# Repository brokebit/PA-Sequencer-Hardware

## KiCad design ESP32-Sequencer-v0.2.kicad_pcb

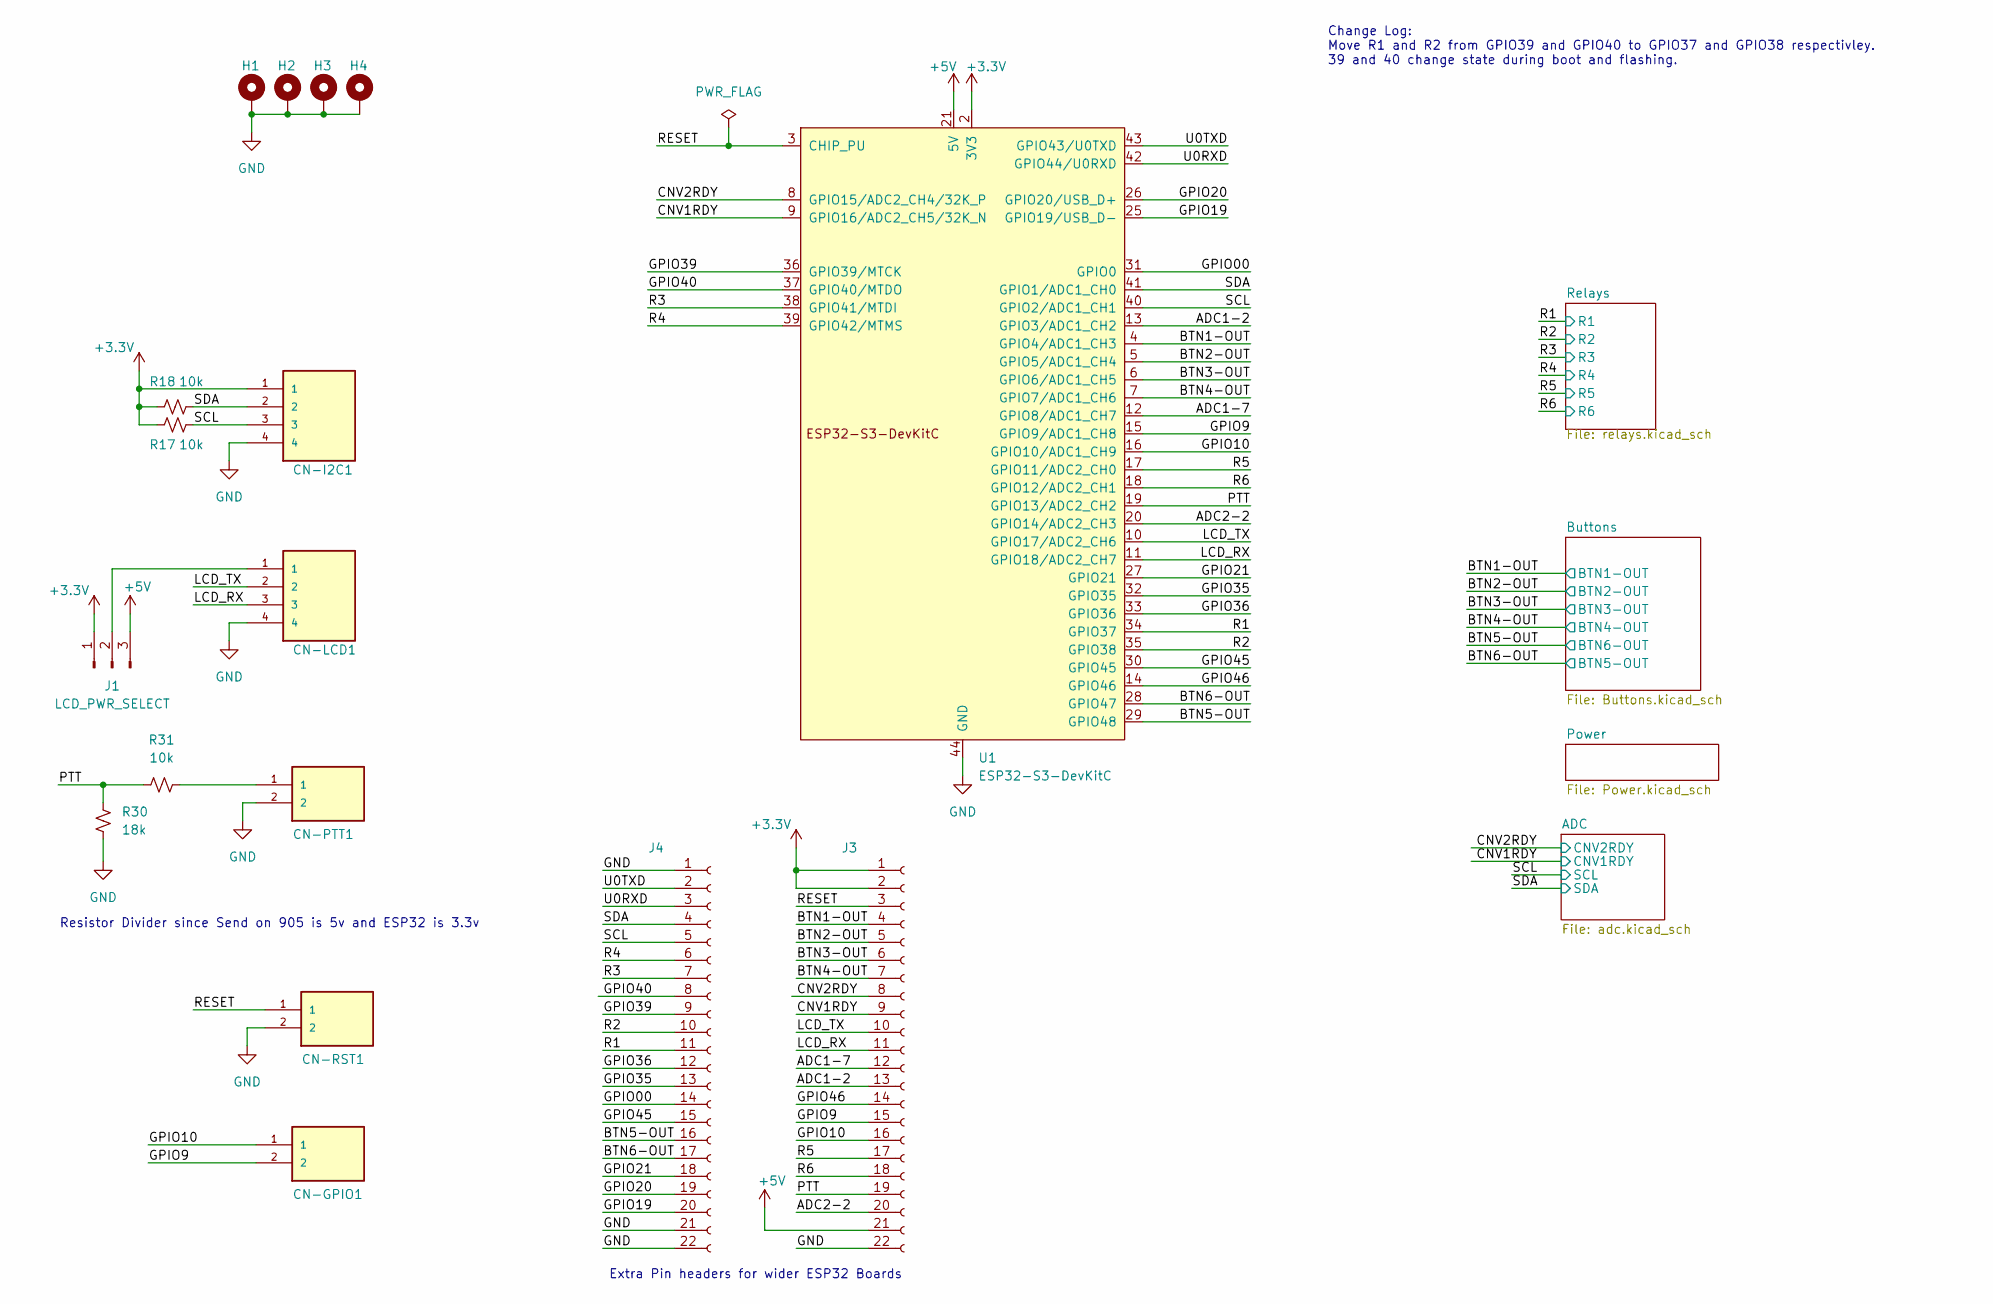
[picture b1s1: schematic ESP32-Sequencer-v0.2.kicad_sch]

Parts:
CN-GPIO1: TBP02R1-381-02OR; CUI_TBP02R1-381-02OR
CN-I2C1: TBP02R1-381-04OR; CUI_TBP02R1-381-04OR
CN-LCD1: TBP02R1-381-04OR; CUI_TBP02R1-381-04OR
CN-PTT1: TBP02R1-381-02OR; CUI_TBP02R1-381-02OR
CN-RST1: TBP02R1-381-02OR; CUI_TBP02R1-381-02OR
H1, H2, H3, H4: MountingHole_Pad; MountingHole_3.2mm_M3_Pad
J1: LCD_PWR_SELECT; PinHeader_1x03_P2.54mm_Vertical
J3, J4: Conn_01x22_Socket; PinSocket_1x22_P2.54mm_Vertical
R17, R18, R31: 10k; R_0805_2012Metric
R30: 18k; R_0805_2012Metric
U1: ESP32-S3-DevKitC

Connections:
+3.3V: CN-I2C1.1, J1.1, J3.1, J3.2, R17.1, R18.1, U1.1 (3V3), U1.2 (3V3); also elsewhere on the board
+5V: J1.3, J3.21, U1.21 (5V); also elsewhere on the board
/ADC1-2: J3.13, U1.13 (GPIO3/ADC1_CH2)
/ADC1-7: J3.12, U1.12 (GPIO8/ADC1_CH7)
/ADC2-2: J3.20, U1.20 (GPIO14/ADC2_CH3)
/BTN1-OUT: J3.4, U1.4 (GPIO4/ADC1_CH3); also elsewhere on the board
/BTN2-OUT: J3.5, U1.5 (GPIO5/ADC1_CH4); also elsewhere on the board
/BTN3-OUT: J3.6, U1.6 (GPIO6/ADC1_CH5); also elsewhere on the board
/BTN4-OUT: J3.7, U1.7 (GPIO7/ADC1_CH6); also elsewhere on the board
/BTN5-OUT: J4.16, U1.29 (GPIO48); also elsewhere on the board
/BTN6-OUT: J4.17, U1.28 (GPIO47); also elsewhere on the board
/CNV1RDY: J3.9, U1.9 (GPIO16/ADC2_CH5/32K_N); also elsewhere on the board
/CNV2RDY: J3.8, U1.8 (GPIO15/ADC2_CH4/32K_P); also elsewhere on the board
/GPIO00: J4.14, U1.31 (GPIO0)
/GPIO9: CN-GPIO1.2, J3.15, U1.15 (GPIO9/ADC1_CH8)
/GPIO10: CN-GPIO1.1, J3.16, U1.16 (GPIO10/ADC1_CH9)
/GPIO19: J4.20, U1.25 (GPIO19/USB_D-)
/GPIO20: J4.19, U1.26 (GPIO20/USB_D+)
/GPIO21: J4.18, U1.27 (GPIO21)
/GPIO35: J4.13, U1.32 (GPIO35)
/GPIO36: J4.12, U1.33 (GPIO36)
/GPIO39: J4.9, U1.36 (GPIO39/MTCK)
/GPIO40: J4.8, U1.37 (GPIO40/MTDO)
/GPIO45: J4.15, U1.30 (GPIO45)
/GPIO46: J3.14, U1.14 (GPIO46)
/LCD_RX: CN-LCD1.3, J3.11, U1.11 (GPIO18/ADC2_CH7)
/LCD_TX: CN-LCD1.2, J3.10, U1.10 (GPIO17/ADC2_CH6)
/PTT: J3.19, R30.1, R31.1, U1.19 (GPIO13/ADC2_CH2)
/R1: J4.11, U1.34 (GPIO37); also elsewhere on the board
/R2: J4.10, U1.35 (GPIO38); also elsewhere on the board
/R3: J4.7, U1.38 (GPIO41/MTDI); also elsewhere on the board
/R4: J4.6, U1.39 (GPIO42/MTMS); also elsewhere on the board
/R5: J3.17, U1.17 (GPIO11/ADC2_CH0); also elsewhere on the board
/R6: J3.18, U1.18 (GPIO12/ADC2_CH1); also elsewhere on the board
/RESET: CN-RST1.1, J3.3, U1.3 (CHIP_PU)
/SCL: CN-I2C1.3, J4.5, R17.2, U1.40 (GPIO2/ADC1_CH1); also elsewhere on the board
/SDA: CN-I2C1.2, J4.4, R18.2, U1.41 (GPIO1/ADC1_CH0); also elsewhere on the board
/U0RXD: J4.3, U1.42 (GPIO44/U0RXD)
/U0TXD: J4.2, U1.43 (GPIO43/U0TXD)
GND: CN-I2C1.4, CN-LCD1.4, CN-PTT1.2, CN-RST1.2, H1.1, H2.1, H3.1, H4.1, J3.22, J4.1, J4.21, J4.22, R30.2, U1.22 (GND), U1.23 (GND), U1.24 (GND), U1.44 (GND); also elsewhere on the board
unnamed: CN-PTT1.1, R31.2
unnamed: CN-LCD1.1, J1.2

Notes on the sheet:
Change Log: Move R1 and R2 from GPIO39 and GPIO40 to GPIO37 and GPIO38 respectivley. 39 and 40 change state during boot and flashing.
Resistor Divider since Send on 905 is 5v and ESP32 is 3.3v
Extra Pin headers for wider ESP32 Boards

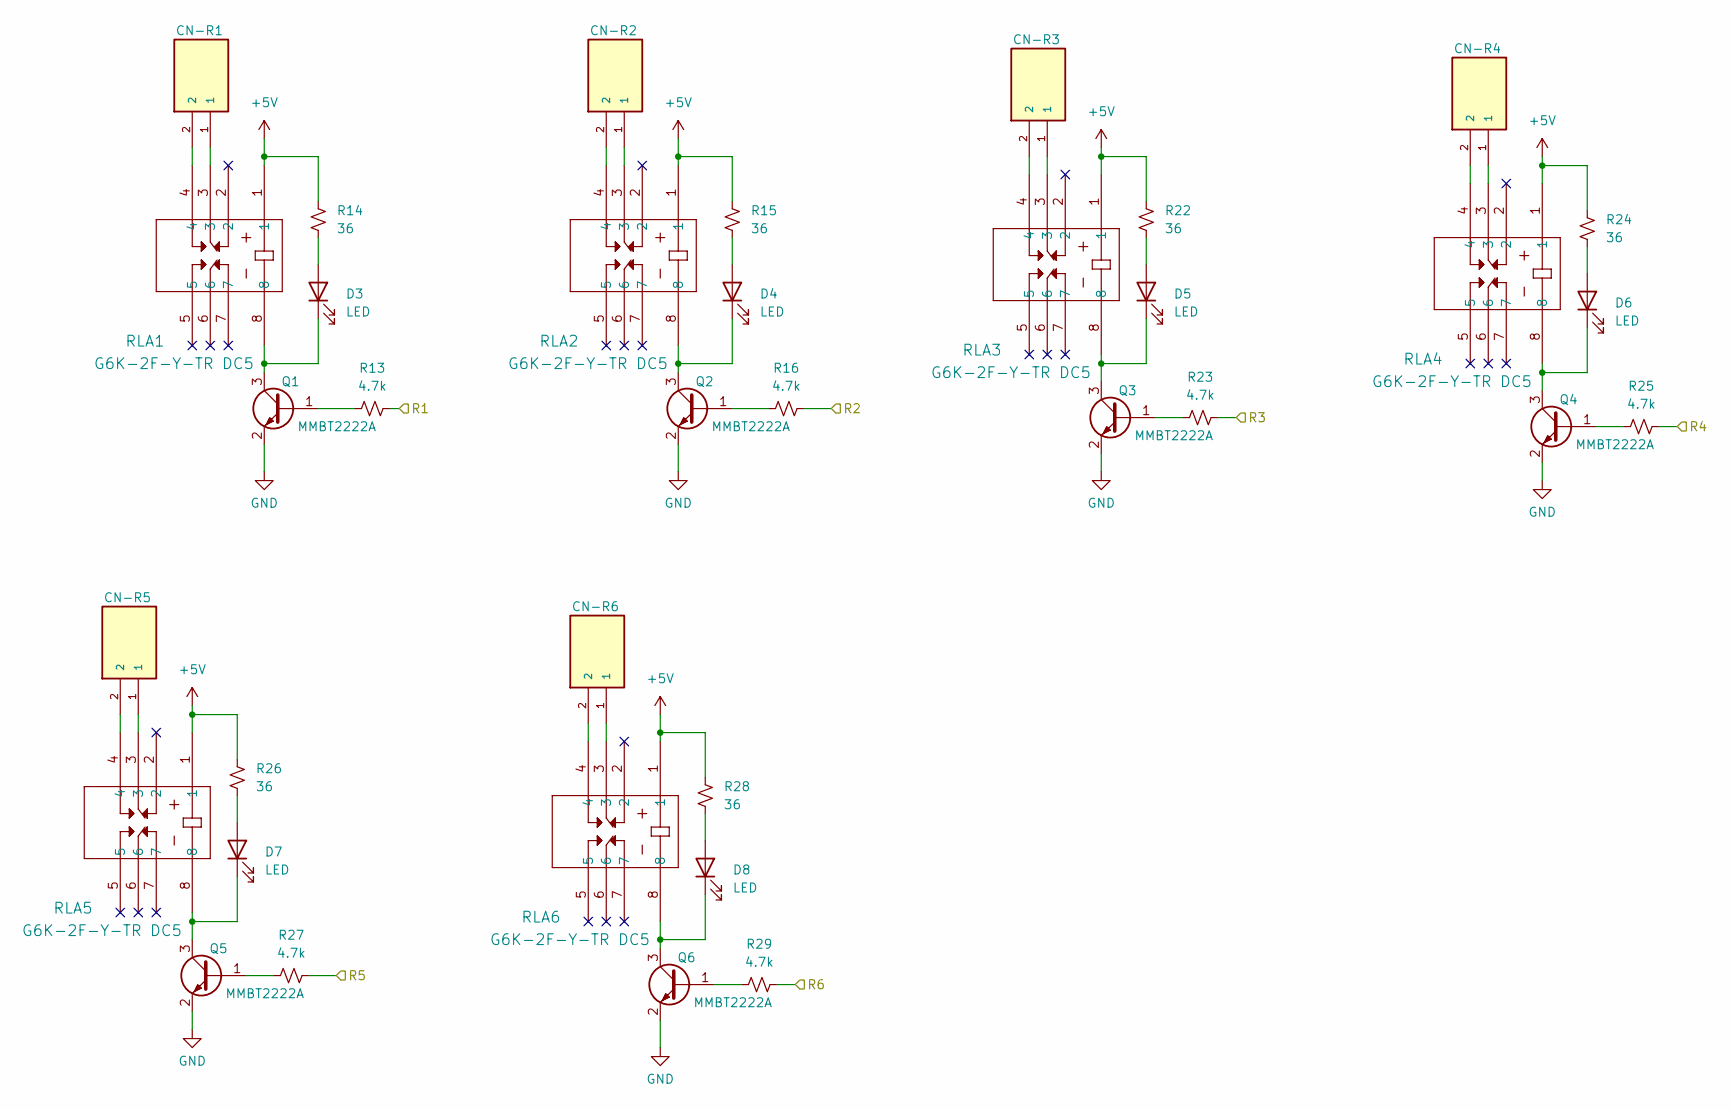
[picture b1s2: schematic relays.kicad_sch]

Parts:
CN-R1, CN-R2, CN-R3, CN-R4, CN-R5, CN-R6: TBP02R1-381-02OR; CUI_TBP02R1-381-02OR
D3, D4, D5, D6, D7, D8: LED; LED_0805_2012Metric; LCSC C84260
Q1, Q2, Q3, Q4, Q5, Q6: MMBT2222A; SOT-23
R13, R16, R23, R25, R27, R29: 4.7k; R_1206_3216Metric
R14, R15, R22, R24, R26, R28: 36; R_0805_2012Metric
RLA1, RLA2, RLA3, RLA4, RLA5, RLA6: G6K-2F-Y-TR DC5; G6K-2F-Y DC3

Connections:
+5V: R14.1, R15.1, R22.1, R24.1, R26.1, R28.1, RLA1.1, RLA2.1, RLA3.1, RLA4.1, RLA5.1, RLA6.1; also elsewhere on the board
/R1: R13.2; also elsewhere on the board
/R2: R16.2; also elsewhere on the board
/R3: R23.2; also elsewhere on the board
/R4: R25.2; also elsewhere on the board
/R5: R27.2; also elsewhere on the board
/R6: R29.2; also elsewhere on the board
GND: Q1.2 (E), Q2.2 (E), Q3.2 (E), Q4.2 (E), Q5.2 (E), Q6.2 (E); also elsewhere on the board
unnamed: CN-R1.1, RLA1.3
unnamed: CN-R1.2, RLA1.4
unnamed: CN-R2.1, RLA2.3
unnamed: CN-R2.2, RLA2.4
unnamed: CN-R3.1, RLA3.3
unnamed: CN-R3.2, RLA3.4
unnamed: CN-R4.1, RLA4.3
unnamed: CN-R4.2, RLA4.4
unnamed: CN-R5.1, RLA5.3
unnamed: CN-R5.2, RLA5.4
unnamed: CN-R6.1, RLA6.3
unnamed: CN-R6.2, RLA6.4
unnamed: D3.2 (A), R14.2
unnamed: D3.1 (K), Q1.3 (C), RLA1.8
unnamed: D4.2 (A), R15.2
unnamed: D4.1 (K), Q2.3 (C), RLA2.8
unnamed: D5.2 (A), R22.2
unnamed: D5.1 (K), Q3.3 (C), RLA3.8
unnamed: D6.2 (A), R24.2
unnamed: D6.1 (K), Q4.3 (C), RLA4.8
unnamed: D7.2 (A), R26.2
unnamed: D7.1 (K), Q5.3 (C), RLA5.8
unnamed: D8.2 (A), R28.2
unnamed: D8.1 (K), Q6.3 (C), RLA6.8
unnamed: Q1.1 (B), R13.1
unnamed: Q2.1 (B), R16.1
unnamed: Q3.1 (B), R23.1
unnamed: Q4.1 (B), R25.1
unnamed: Q5.1 (B), R27.1
unnamed: Q6.1 (B), R29.1

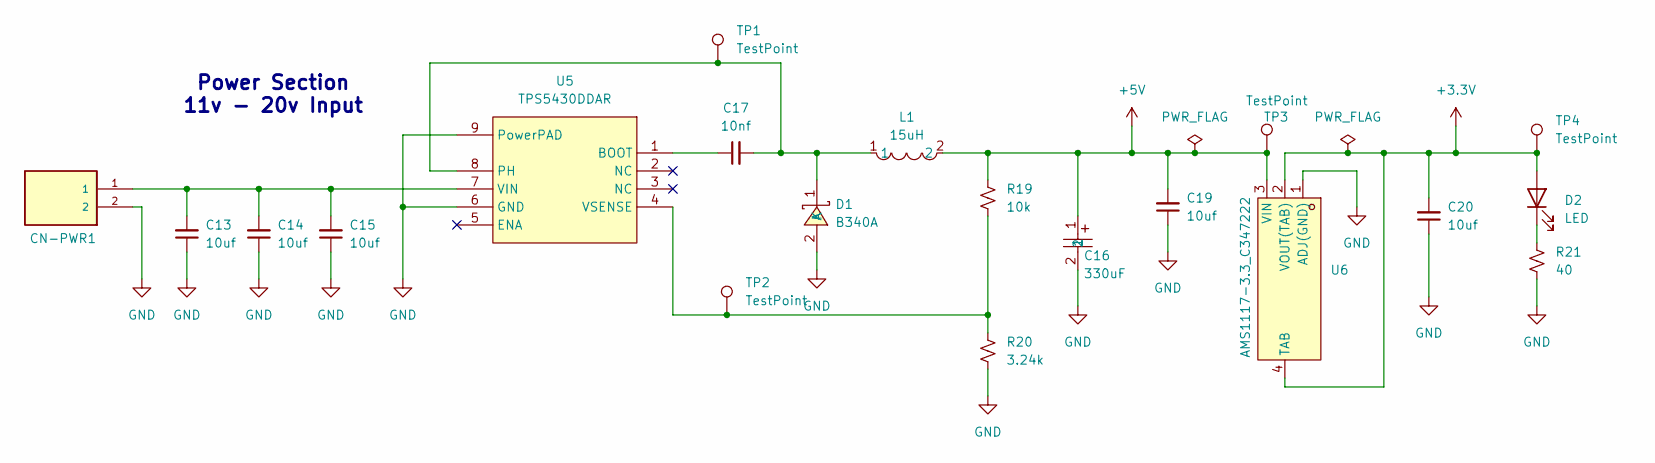
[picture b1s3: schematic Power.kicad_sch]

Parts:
C13, C14, C15, C19, C20: 10uf; C_0603_1608Metric
C16: 330uF; CAP-SMD_L7.3-W4.3-R-RD; LCSC Part C79112
C17: 10nf; C_0603_1608Metric
CN-PWR1: TBP02R1-381-02OR; CUI_TBP02R1-381-02OR
D1: B340A; SMA_L4.3-W2.6-LS5.1-RD; LCSC Part C64982
D2: LED; LED_0805_2012Metric; LCSC Part C84260
L1: 15uH; IND-SMD_L12.5-W12.5_RLF12545T; LCSC Part C40000
R19: 10k; R_0603_1608Metric
R20: 3.24k; R_0603_1608Metric
R21: 40; R_0805_2012Metric; LCSC Part C2930194
TP1, TP2, TP3, TP4: TestPoint; TestPoint_Pad_1.5x1.5mm
U5: TPS5430DDAR; ESOP-8_L4.9-W3.9-P1.27-LS6.0-TL-EP; LCSC Part C9864
U6: AMS1117-3.3_C347222; SOT-223-4_L6.5-W3.5-P2.30-LS7.0-BR; LCSC Part C347222

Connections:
+3.3V: C20.2, D2.2 (A), TP4.1, U6.2 (VOUT(TAB)), U6.4 (TAB); also elsewhere on the board
+5V: C16.1, C19.2, L1.2, R19.1, TP3.1, U6.3 (VIN); also elsewhere on the board
GND: C13.1, C14.1, C15.1, C16.2, C19.1, C20.1, CN-PWR1.2, D1.2 (A), R20.2, R21.2, U5.6 (GND), U5.9 (PowerPAD), U6.1 (ADJ(GND)); also elsewhere on the board
unnamed: C17.2, D1.1 (K), L1.1, TP1.1, U5.8 (PH)
unnamed: D2.1 (K), R21.1
unnamed: C17.1, U5.1 (BOOT)
unnamed: C13.2, C14.2, C15.2, CN-PWR1.1, U5.7 (VIN)
unnamed: R19.2, R20.1, TP2.1, U5.4 (VSENSE)

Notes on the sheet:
Power Section 11v - 20v Input

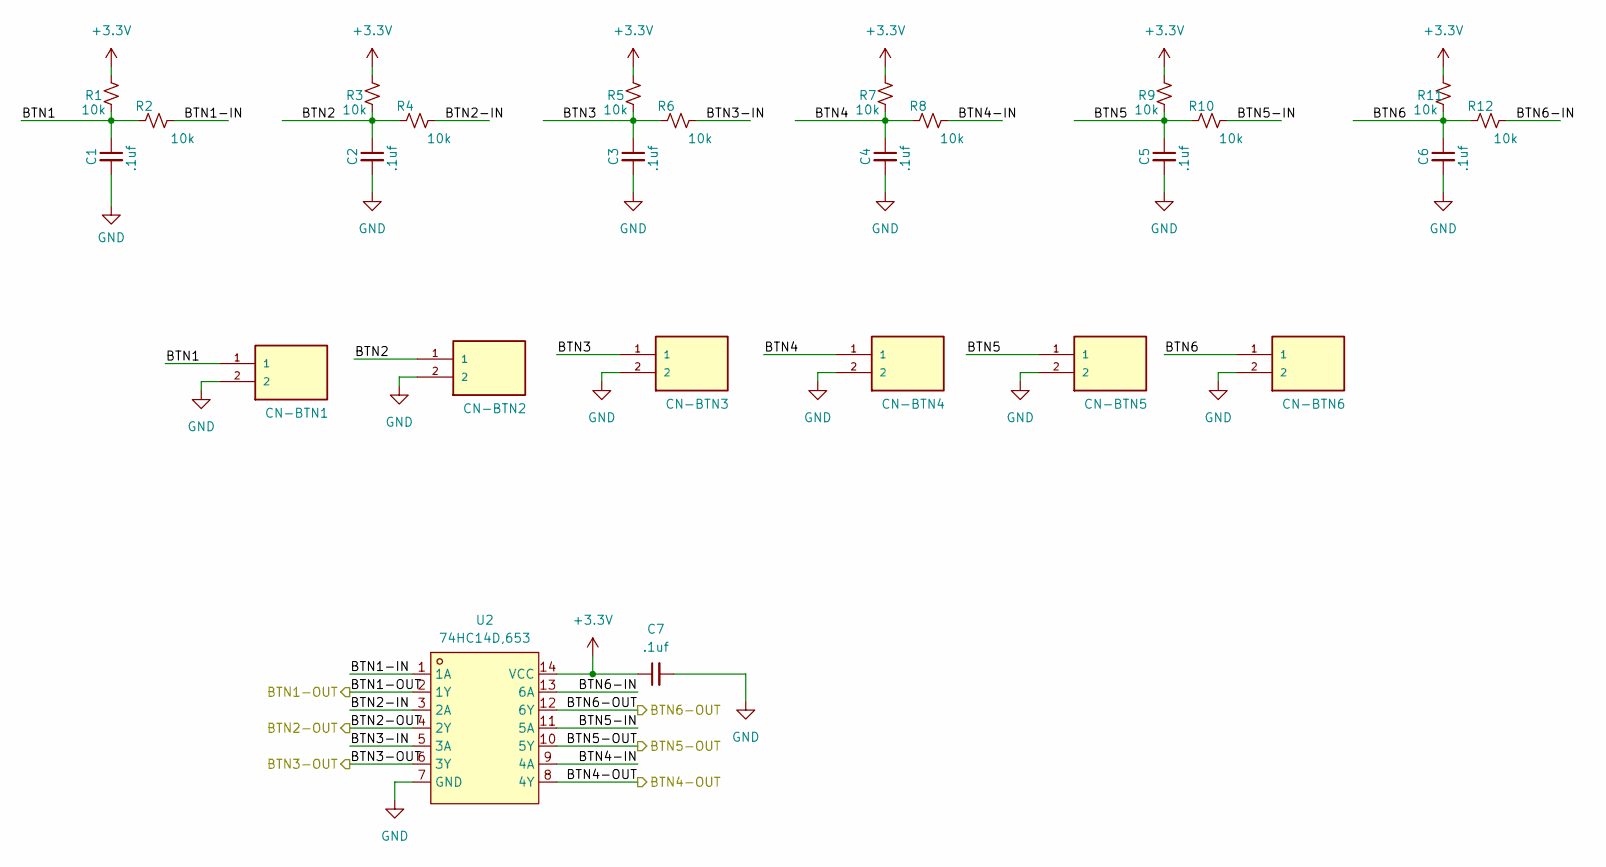
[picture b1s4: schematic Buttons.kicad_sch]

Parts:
C1, C2, C3, C4, C5, C6, C7: .1uf; C_0805_2012Metric
CN-BTN1, CN-BTN2, CN-BTN3, CN-BTN4, CN-BTN5, CN-BTN6: TBP02R1-381-02OR; CUI_TBP02R1-381-02OR
R1, R2, R3, R4, R5, R6, R7, R8, R9, R10, R11, R12: 10k; R_0805_2012Metric
U2: 74HC14D,653; SOIC-14_L8.7-W3.9-P1.27-LS6.0-BL; LCSC Part C5605

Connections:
+3.3V: C7.1, R1.1, R3.1, R5.1, R7.1, R9.1, R11.1, U2.14 (VCC); also elsewhere on the board
/BTN1-OUT: U2.2 (1Y); also elsewhere on the board
/BTN2-OUT: U2.4 (2Y); also elsewhere on the board
/BTN3-OUT: U2.6 (3Y); also elsewhere on the board
/BTN4-OUT: U2.8 (4Y); also elsewhere on the board
/BTN5-OUT: U2.12 (6Y); also elsewhere on the board
/BTN6-OUT: U2.10 (5Y); also elsewhere on the board
/Buttons/BTN1: C1.1, CN-BTN1.1, R1.2, R2.2
/Buttons/BTN1-IN: R2.1, U2.1 (1A)
/Buttons/BTN2: C2.1, CN-BTN2.1, R3.2, R4.2
/Buttons/BTN2-IN: R4.1, U2.3 (2A)
/Buttons/BTN3: C3.1, CN-BTN3.1, R5.2, R6.2
/Buttons/BTN3-IN: R6.1, U2.5 (3A)
/Buttons/BTN4: C4.1, CN-BTN4.1, R7.2, R8.2
/Buttons/BTN4-IN: R8.1, U2.9 (4A)
/Buttons/BTN5: C5.1, CN-BTN5.1, R9.2, R10.2
/Buttons/BTN5-IN: R10.1, U2.11 (5A)
/Buttons/BTN6: C6.1, CN-BTN6.1, R11.2, R12.2
/Buttons/BTN6-IN: R12.1, U2.13 (6A)
GND: C1.2, C2.2, C3.2, C4.2, C5.2, C6.2, C7.2, CN-BTN1.2, CN-BTN2.2, CN-BTN3.2, CN-BTN4.2, CN-BTN5.2, CN-BTN6.2, U2.7 (GND); also elsewhere on the board

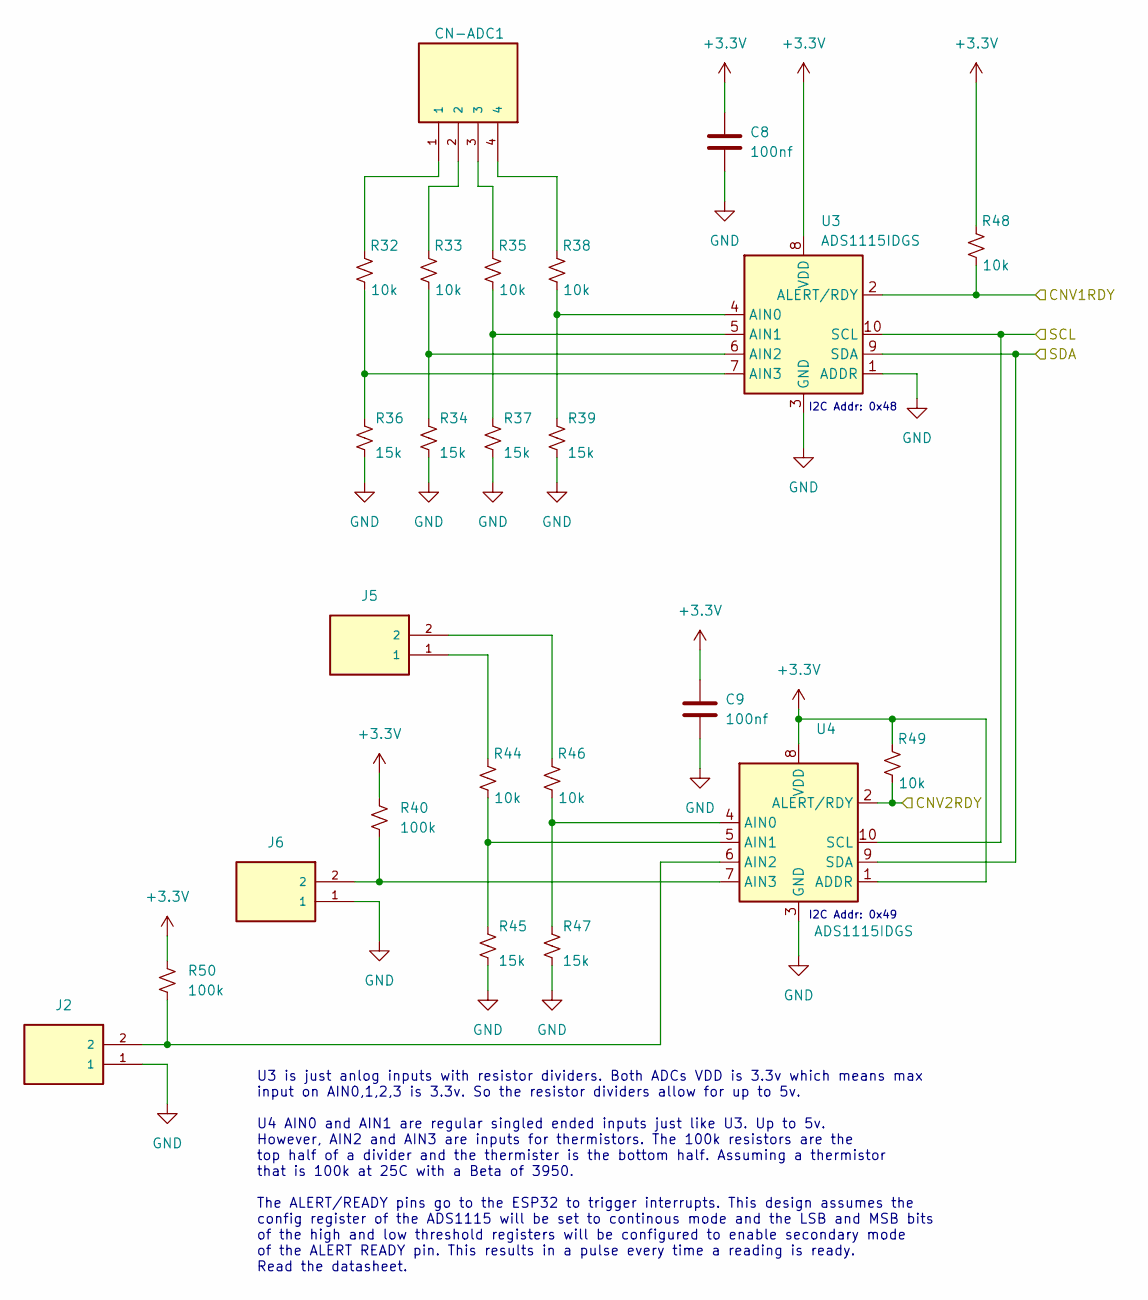
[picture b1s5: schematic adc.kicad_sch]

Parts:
C8, C9: 100nf; C_0805_2012Metric
CN-ADC1: TBP02R1-381-04OR; CUI_TBP02R1-381-04OR
J2, J5, J6: TBP02R1-381-02OR; CUI_TBP02R1-381-02OR
R32, R33, R35, R38, R44, R46, R48, R49: 10k; R_0805_2012Metric
R34, R36, R37, R39, R45, R47: 15k; R_0805_2012Metric
R40, R50: 100k; R_0805_2012Metric
U3, U4: ADS1115IDGS; TSSOP-10_3x3mm_P0.5mm

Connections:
+3.3V: C8.1, C9.1, R40.1, R48.1, R49.1, R50.1, U3.8 (VDD), U4.1 (ADDR), U4.8 (VDD); also elsewhere on the board
/CNV1RDY: R48.2, U3.2 (ALERT/RDY); also elsewhere on the board
/CNV2RDY: R49.2, U4.2 (ALERT/RDY); also elsewhere on the board
/SCL: U3.10 (SCL), U4.10 (SCL); also elsewhere on the board
/SDA: U3.9 (SDA), U4.9 (SDA); also elsewhere on the board
GND: C8.2, C9.2, J2.1, J6.1, R34.2, R36.2, R37.2, R39.2, R45.2, R47.2, U3.1 (ADDR), U3.3 (GND), U4.3 (GND); also elsewhere on the board
unnamed: CN-ADC1.1, R32.1
unnamed: CN-ADC1.2, R33.1
unnamed: CN-ADC1.3, R35.1
unnamed: CN-ADC1.4, R38.1
unnamed: J5.1, R44.1
unnamed: J5.2, R46.1
unnamed: R38.2, R39.1, U3.4 (AIN0)
unnamed: R35.2, R37.1, U3.5 (AIN1)
unnamed: R33.2, R34.1, U3.6 (AIN2)
unnamed: R32.2, R36.1, U3.7 (AIN3)
unnamed: R46.2, R47.1, U4.4 (AIN0)
unnamed: R44.2, R45.1, U4.5 (AIN1)
unnamed: J2.2, R50.2, U4.6 (AIN2)
unnamed: J6.2, R40.2, U4.7 (AIN3)

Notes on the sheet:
U3 is just anlog inputs with resistor dividers. Both ADCs VDD is 3.3v which means max input on AIN0,1,2,3 is 3.3v. So the resistor dividers allow for up to 5v. U4 AIN0 and AIN1 are regular singled ended inputs just like U3. Up to 5v. However, AIN2 and AIN3 are inputs for thermistors. The 100k resis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
I2C Addr: 0x48
I2C Addr: 0x49

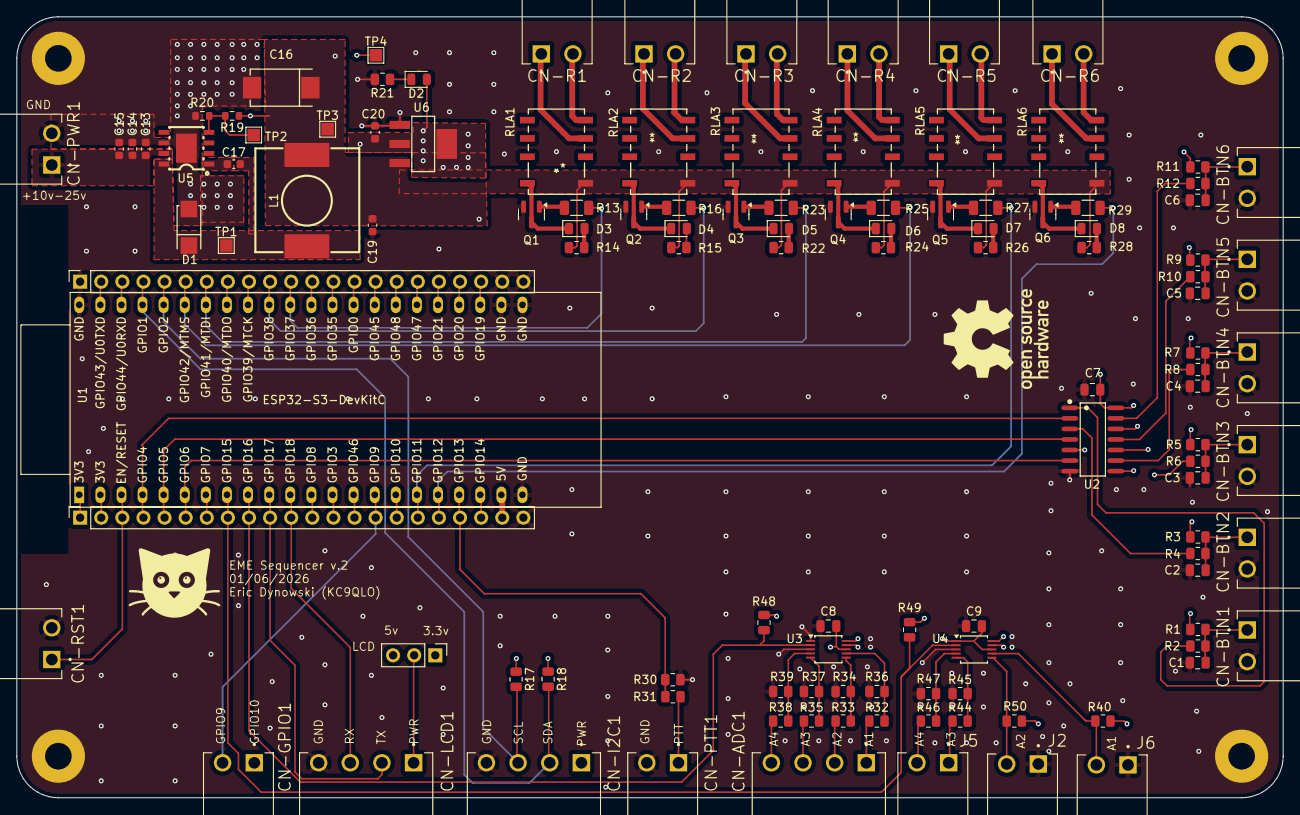
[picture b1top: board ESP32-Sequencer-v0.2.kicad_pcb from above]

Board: 6 copper layers, 152.4 x 94.0 mm, 123 parts (0 on the bottom side), 103 nets.

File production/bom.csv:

Designator,Footprint,Quantity,Value,LCSC Part #
"C1, C2, C3, C4, C5, C6, C7",0805,7,.1uf,
"C13, C14, C15, C19, C20",0603,5,10uf,
C16,CAP-SMD_L7.3-W4.3-R-RD,1,330uF,C79112
C17,0603,1,10nf,
"C8, C9",0805,2,100nf,
"CN-ADC1, CN-I2C1, CN-LCD1",CUI_TBP02R1-381-04OR,3,TBP02R1-381-04OR,
"CN-BTN1, CN-BTN2, CN-BTN3, CN-BTN4, CN-BTN5, CN-BTN6, CN-GPIO1, CN-PTT1, CN-PWR1, CN-R1, CN-R2, CN-R3, CN-R4, CN-R5, CN-R6, CN-RST1, J2, J5, J6",CUI_TBP02R1-381-02OR,19,TBP02R1-381-02OR,
D1,SMA_L4.3-W2.6-LS5.1-RD,1,B340A,C64982
"D2, D3, D4, D5, D6, D7, D8",0805,7,LED,C84260
J1,PinHeader_1x03_P2.54mm_Vertical,1,LCD_PWR_SELECT,
"J3, J4",PinSocket_1x22_P2.54mm_Vertical,2,Conn_01x22_Socket,
L1,IND-SMD_L12.5-W12.5_RLF12545T,1,15uH,C40000
"Q1, Q2, Q3, Q4, Q5, Q6",SOT-23,6,MMBT2222A,
"R1, R10, R11, R12, R17, R18, R2, R3, R31, R32, R33, R35, R38, R4, R44, R46, R48, R49, R5, R6, R7, R8, R9",0805,23,10k,
"R13, R16, R23, R25, R27, R29",1206,6,4.7k,
"R14, R15, R22, R24, R26, R28",0805,6,36,
R19,0603,1,10k,
R20,0603,1,3.24k,
R21,0805,1,40,C2930194
R30,0805,1,18k,
"R34, R36, R37, R39, R45, R47",0805,6,15k,
"R40, R50",0805,2,100k,
"RLA1, RLA2, RLA3, RLA4, RLA5, RLA6",G6K-2F-Y DC3,6,G6K-2F-Y-TR DC5,
"TP1, TP2, TP3, TP4",TestPoint_Pad_1.5x1.5mm,4,TestPoint,
U1,ESP32-S3-DevKitC,1,ESP32-S3-DevKitC,
U2,SOIC-14_L8.7-W3.9-P1.27-LS6.0-BL,1,"74HC14D,653",C5605
"U3, U4",TSSOP-10_3x3mm_P0.5mm,2,ADS1115IDGS,
U5,ESOP-8_L4.9-W3.9-P1.27-LS6.0-TL-EP,1,TPS5430DDAR,C9864
U6,SOT-223-4_L6.5-W3.5-P2.30-LS7.0-BR,1,AMS1117-3.3_C347222,C347222

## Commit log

2026-03-26 Add picture
